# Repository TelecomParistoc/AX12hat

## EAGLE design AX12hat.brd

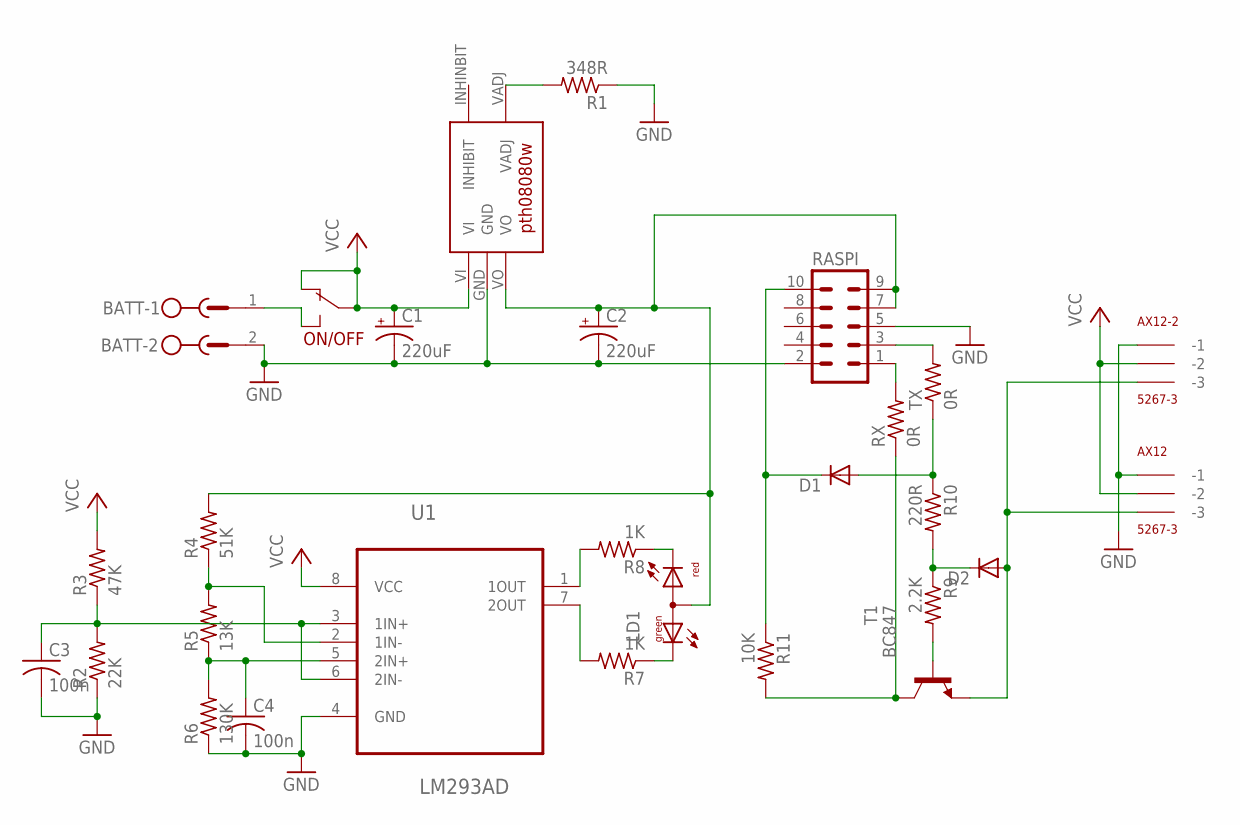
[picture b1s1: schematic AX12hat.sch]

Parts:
AX12, AX12-2: 5267-3
BATT: MSTBV2
C1, C2: 220uF; E2,5-7
C3, C4: 100n; C0805
D1, D2: DIODE-SOD523; SOD523
LD1: DUOLED-RG-A; DUOLED-A-5MM
ON/OFF: SWITCH
R1: 348R; R0805
R2: 22K; R0805
R3: 47K; R0805
R4: 51K; R0805
R5: 13K; R0805
R6: 130K; R0805
R7, R8: 1K; R0805
R9: 2.2K; R0805
R10: 220R; R0805
R11: 10K; R0805
RASPI: MA05-2
RX: 0R; R0805
T1: BC847; SOT23
TX: 0R; R0805
U1: LM293AD; SOIC127P600X175-8N
U$1: REGUL_PTH

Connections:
GND: AX12.P$1 (-1), AX12-2.P$1 (-1), BATT.2, C1.-, C2.-, C3.2, C4.2, R1.1, R2.1, R6.1, RASPI.2, RASPI.5, U1.4 (GND), U$1.GND
unnamed: C2.+, LD1.A, R4.2, RASPI.7, RASPI.9, U$1.VO
unnamed: R1.2, U$1.VADJ
unnamed: R8.2, U1.1 (1OUT)
unnamed: LD1.CR, R8.1
unnamed: R7.2, U1.7 (2OUT)
unnamed: LD1.CX (CG), R7.1
unnamed: D2.C, R9.1, R10.2
unnamed: AX12.P$3 (-3), AX12-2.P$3 (-3), D2.A, T1.2 (E)
unnamed: C3.1, R2.2, R3.1, U1.3 (1IN+), U1.6 (2IN-)
unnamed: R4.1, R5.2, U1.2 (1IN-)
unnamed: C4.1, R5.1, R6.2, U1.5 (2IN+)
unnamed: R9.2, T1.1 (B)
unnamed: D1.C, R11.1, RASPI.10
unnamed: RASPI.1, RX.2
unnamed: RASPI.3, TX.2
unnamed: D1.A, R10.1, TX.1
unnamed: R11.2, RX.1, T1.3 (C)
unnamed: BATT.1, ON/OFF.P$3 (3)
VCC: AX12.P$2 (-2), AX12-2.P$2 (-2), C1.+, ON/OFF.P$1 (1), ON/OFF.P$2 (2), R3.2, U1.8 (VCC), U$1.VI

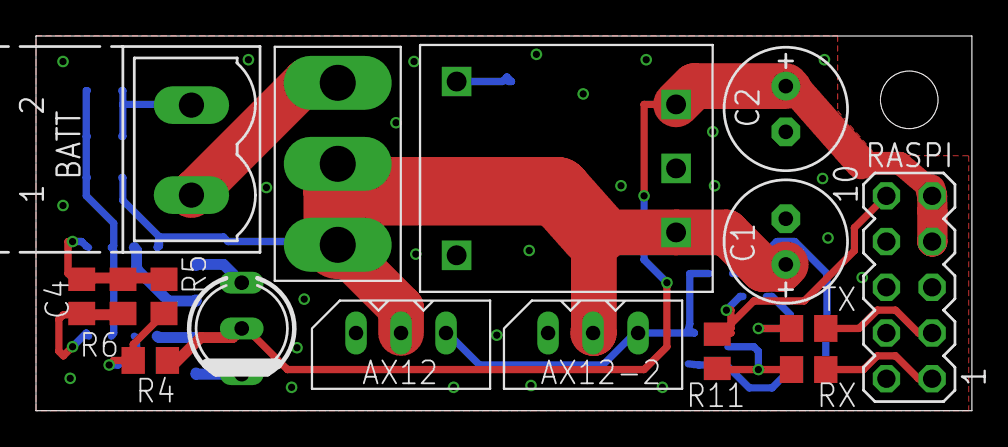
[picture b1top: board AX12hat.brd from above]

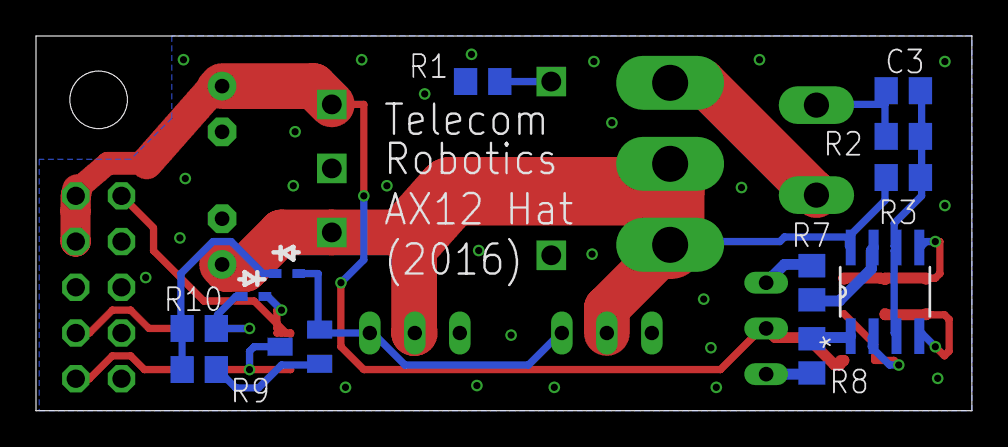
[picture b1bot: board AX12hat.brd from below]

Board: 2 copper layers, 52.0 x 20.8 mm, 28 parts (12 on the bottom side), 20 nets.

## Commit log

2016-09-18 created schematic and PCB
